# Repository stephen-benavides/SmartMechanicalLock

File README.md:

# SmartMechanicalLock
Project contains all elements from the design of the PCB for the mechanical locks and its components as well as the mobile application to access the app to send the necessary commands to lock/unlock the lock and to store all sensible information within the cache of the android device

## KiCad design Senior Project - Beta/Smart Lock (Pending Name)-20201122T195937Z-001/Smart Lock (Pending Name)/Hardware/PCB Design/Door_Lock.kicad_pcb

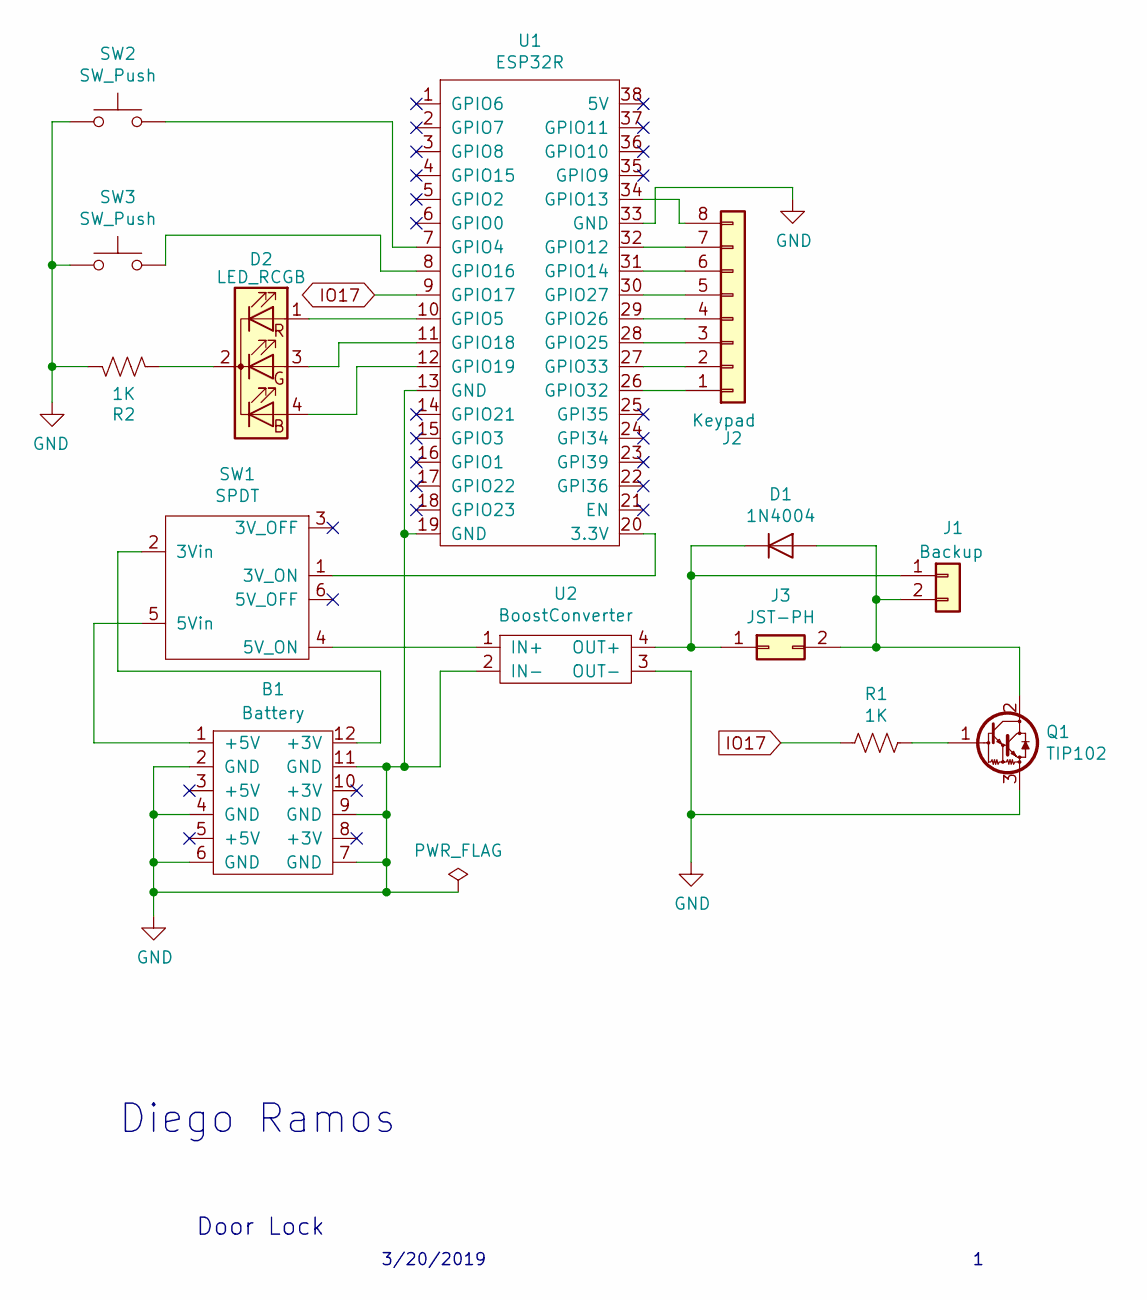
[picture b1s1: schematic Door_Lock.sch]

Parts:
B1: Battery; Battery_Supply
D1: 1N4004; D_DO-41_SOD81_P5.08mm_Vertical_AnodeUp
D2: LED_RCGB; LED_D5.0mm-4_RGB_Staggered_Pins
J1: Backup; PinHeader_1x02_P2.54mm_Vertical
J2: Keypad; PinSocket_1x08_P2.54mm_Vertical
J3: JST-PH
Q1: TIP102; TO-220-3_Vertical
R1: 1K; R_Axial_DIN0207_L6.3mm_D2.5mm_P7.62mm_Horizontal
R2: 1K; R_Axial_DIN0207_L6.3mm_D2.5mm_P2.54mm_Vertical
SW1: SPDT; PinSocket_2x03_P2.54mm_Vertical
SW2, SW3: SW_Push; SW_PUSH_6mm_H5mm
U1: ESP32R; ESP32_Diego
U2: BoostConverter

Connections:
GND: B1.2 (GND), B1.4 (GND), B1.6 (GND), B1.7 (GND), B1.9 (GND), B1.11 (GND), Q1.3, R2.2, SW2.1, SW3.1, U1.13 (GND), U1.19 (GND), U1.33 (GND), U2.2 (IN-), U2.3 (OUT-)
IO17: R1.2, U1.9 (GPIO17)
unnamed: B1.1 (+5V), SW1.5 (5Vin)
unnamed: B1.12 (+3V), SW1.2 (3Vin)
unnamed: D1.1 (K), J1.1, J3.1, U2.4 (OUT+)
unnamed: D1.2 (A), J1.2, J3.2, Q1.2
unnamed: D2.1 (RA), U1.10 (GPIO5)
unnamed: D2.2 (K), R2.1
unnamed: D2.3 (GA), U1.11 (GPIO18)
unnamed: D2.4 (BA), U1.12 (GPIO19)
unnamed: J2.1, U1.26 (GPIO32)
unnamed: J2.2, U1.27 (GPIO33)
unnamed: J2.3, U1.28 (GPIO25)
unnamed: J2.4, U1.29 (GPIO26)
unnamed: J2.5, U1.30 (GPIO27)
unnamed: J2.6, U1.31 (GPIO14)
unnamed: J2.7, U1.32 (GPIO12)
unnamed: J2.8, U1.34 (GPIO13)
unnamed: Q1.1, R1.1
unnamed: SW1.1 (3V_ON), U1.20 (3.3V)
unnamed: SW1.4 (5V_ON), U2.1 (IN+)
unnamed: SW2.2, U1.7 (GPIO4)
unnamed: SW3.2, U1.8 (GPIO16)

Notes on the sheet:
Door Lock
3/20/2019
Diego Ramos

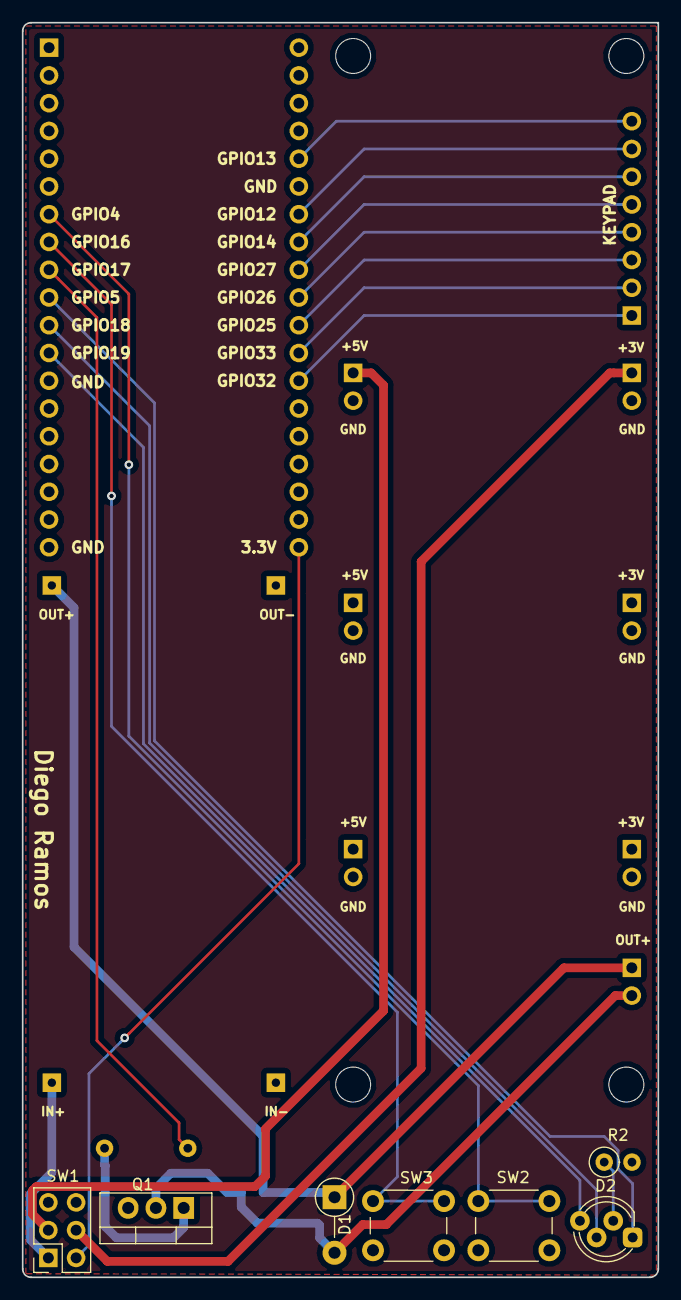
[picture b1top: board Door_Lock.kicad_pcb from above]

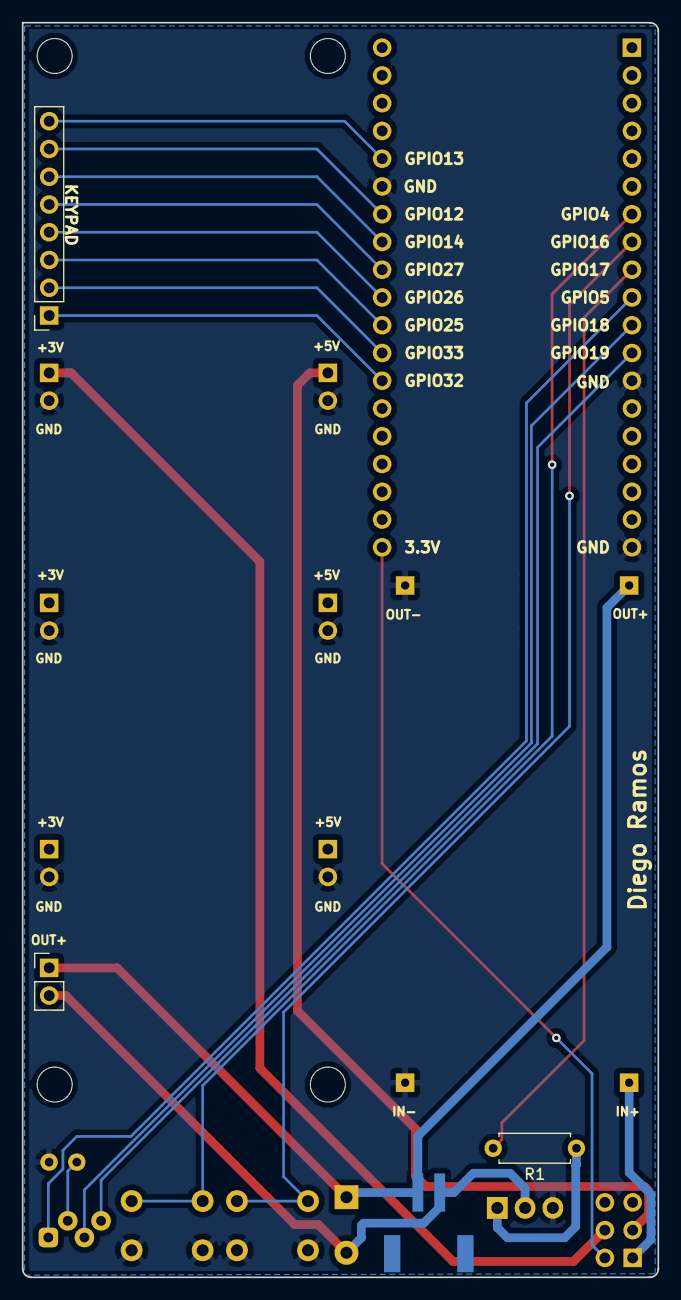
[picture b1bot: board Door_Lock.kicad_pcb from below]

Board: 2 copper layers, 58.2 x 114.8 mm, 16 parts (4 on the bottom side), 23 nets.

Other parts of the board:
HOLE1, HOLE3: MountingHole_3.2mm_M3
